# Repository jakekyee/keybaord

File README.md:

# Keyboard

## Quick Summary
A split inspired by the Quefrency.

# Build Guide
 - Placeholder
## BOM
 - Placeholder

# Firmware
https://github.com/jakekyee/zmk-config-stuff

# Techincal Notes  
The wiring on the right side is kinda crazy because I didn't really know what I was doing in KiCad. Here's the reference I used when writing the firmware.

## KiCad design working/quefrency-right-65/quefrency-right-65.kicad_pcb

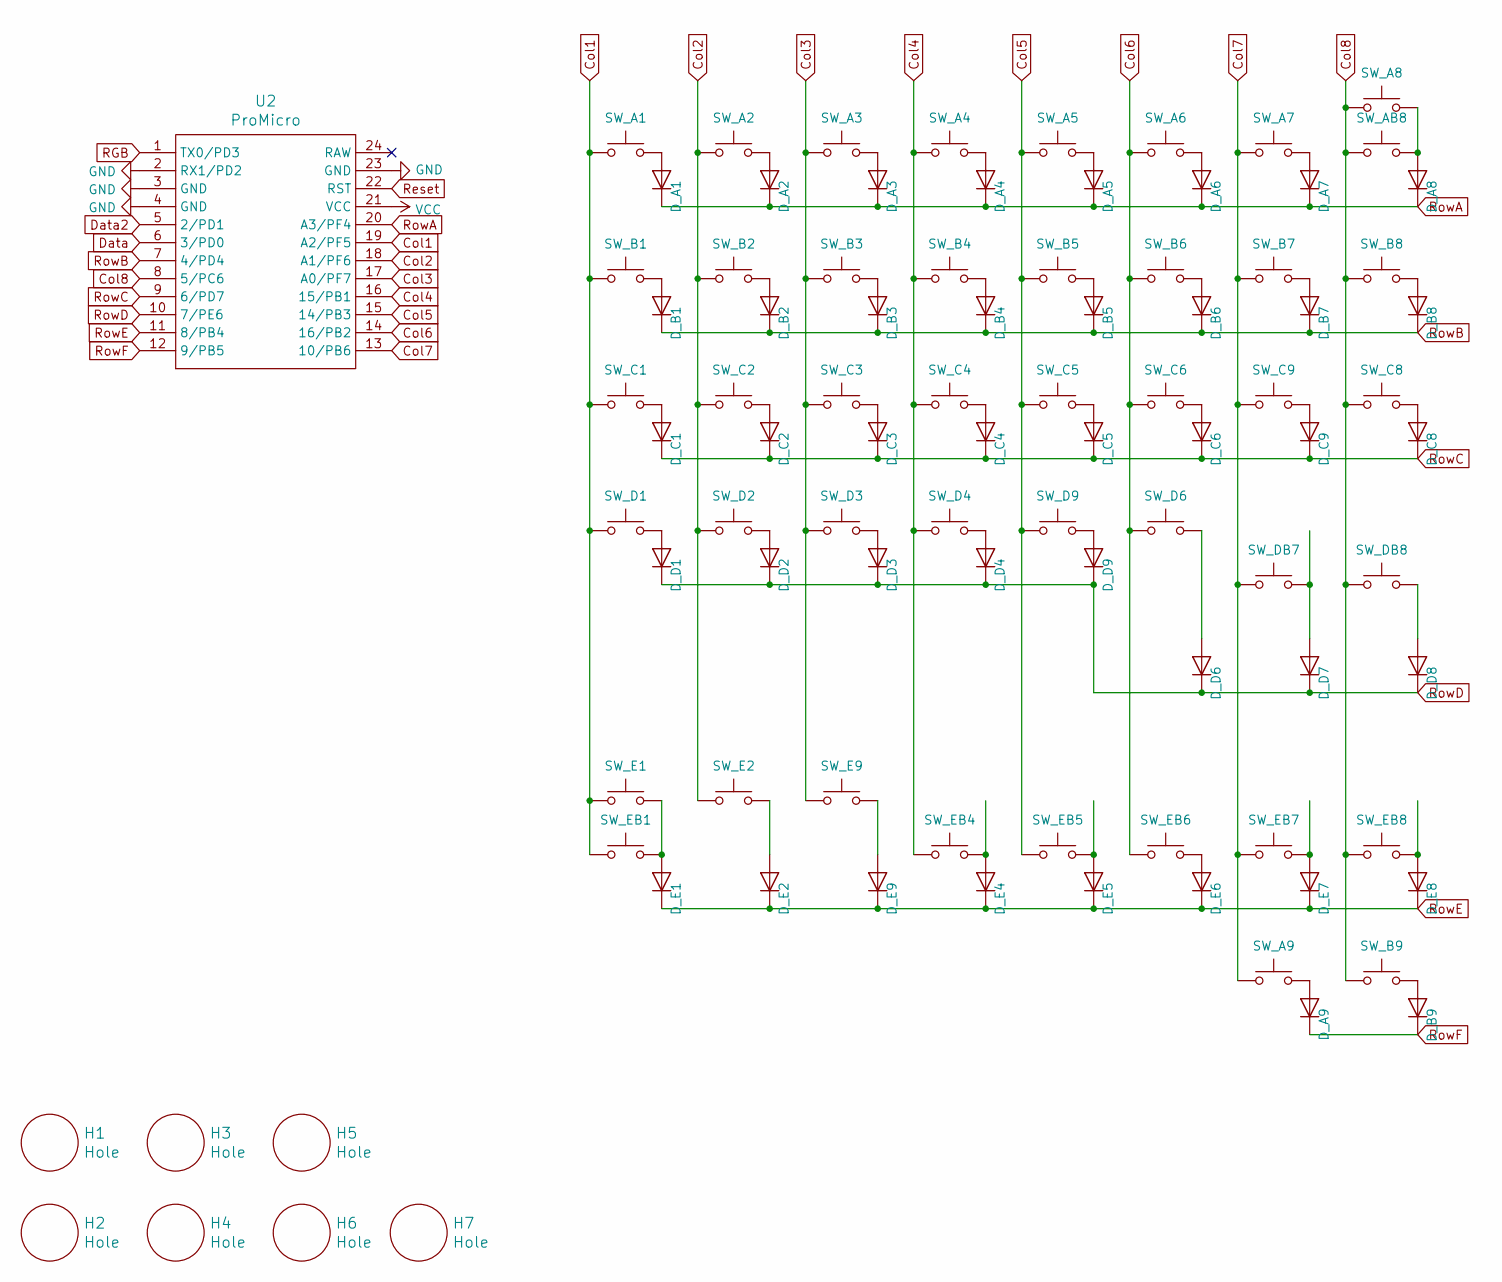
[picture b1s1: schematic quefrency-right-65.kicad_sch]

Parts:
D_A1, D_A2, D_A3, D_A4, D_A5, D_A6, D_A7, D_A8, D_A9: D; D_SOD-123
D_B1, D_B2, D_B3, D_B4, D_B5, D_B6, D_B7, D_B8, D_B9: D; D_SOD-123
D_C1, D_C2, D_C3, D_C4, D_C5, D_C6, D_C8, D_C9: D; D_SOD-123
D_D1, D_D2, D_D3, D_D4, D_D6, D_D7, D_D8, D_D9: D; D_SOD-123
D_E1, D_E2, D_E4, D_E5, D_E6, D_E7, D_E8, D_E9: D; D_SOD-123
H1, H2, H3, H4, H5, H6, H7: Hole; MountingHole_3.2mm_M3_ISO14580_Pad
SW_A1, SW_A2, SW_A3, SW_A4, SW_A5, SW_A6, SW_A9: SW_Push; ChocMX
SW_A7: SW_Push; ChocMX_sameside
SW_A8: SW_Push; ChocMX_sameside_flippedpads_2.25U
SW_AB8: SW_Push; ChocMX_sameside
SW_B1, SW_B2, SW_B3, SW_B4, SW_B5, SW_B6, SW_B7: SW_Push; ChocMX
SW_B8, SW_B9: SW_Push; ChocMX_sameside_flippedpads
SW_C1, SW_C2, SW_C3, SW_C4, SW_C5, SW_C6, SW_C9: SW_Push; ChocMX
SW_C8: SW_Push; ChocMX_flippedpads_2.25U
SW_D1, SW_D2, SW_D3, SW_D4, SW_D6, SW_D9: SW_Push; ChocMX
SW_DB7, SW_DB8: SW_Push; ChocMX
SW_E1: SW_Push; ChocMX_sameside_flippedpads_2.25U
SW_E2: SW_Push; ChocMX_sameside_flippedpads
SW_E9: SW_Push; ChocMX
SW_EB1: SW_Push; ChocMX_sameside
SW_EB4, SW_EB5, SW_EB6, SW_EB7, SW_EB8: SW_Push; ChocMX
U2: ProMicro; ArduinoProMicro-ZigZag

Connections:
Col1: SW_A1.1, SW_B1.1, SW_C1.1, SW_D1.1, SW_E1.1, SW_EB1.1, U2.19 (A2/PF5)
Col2: SW_A2.1, SW_B2.1, SW_C2.1, SW_D2.1, SW_E2.1, U2.18 (A1/PF6)
Col3: SW_A3.1, SW_B3.1, SW_C3.1, SW_D3.1, SW_E9.1, U2.17 (A0/PF7)
Col4: SW_A4.1, SW_B4.1, SW_C4.1, SW_D4.1, SW_EB4.1, U2.16 (15/PB1)
Col5: SW_A5.1, SW_B5.1, SW_C5.1, SW_D9.1, SW_EB5.2, U2.15 (14/PB3)
Col6: SW_A6.1, SW_B6.1, SW_C6.1, SW_D6.1, SW_EB6.1, U2.14 (16/PB2)
Col7: SW_A7.1, SW_A9.1, SW_B7.1, SW_C9.1, SW_DB7.1, SW_EB7.2, U2.13 (10/PB6)
Col8: SW_A8.1, SW_AB8.1, SW_B8.1, SW_B9.1, SW_C8.1, SW_DB8.1, SW_EB8.1, U2.8 (5/PC6)
Data: U2.6 (3/PD0)
Data2: U2.5 (2/PD1)
GND: U2.2 (RX1/PD2), U2.3 (GND), U2.4 (GND), U2.23 (GND)
unnamed: D_A1.2 (A), SW_A1.2
unnamed: D_A2.2 (A), SW_A2.2
unnamed: D_A3.2 (A), SW_A3.2
unnamed: D_A4.2 (A), SW_A4.2
unnamed: D_A5.2 (A), SW_A5.2
unnamed: D_A6.2 (A), SW_A6.2
unnamed: D_A7.2 (A), SW_A7.2
unnamed: D_A8.2 (A), SW_A8.2, SW_AB8.2
unnamed: D_A9.2 (A), SW_A9.2
unnamed: D_B1.2 (A), SW_B1.2
unnamed: D_B2.2 (A), SW_B2.2
unnamed: D_B3.2 (A), SW_B3.2
unnamed: D_B4.2 (A), SW_B4.2
unnamed: D_B5.2 (A), SW_B5.2
unnamed: D_B6.2 (A), SW_B6.2
unnamed: D_B7.2 (A), SW_B7.2
unnamed: D_B8.2 (A), SW_B8.2
unnamed: D_B9.2 (A), SW_B9.2
unnamed: D_C1.2 (A), SW_C1.2
unnamed: D_C2.2 (A), SW_C2.2
unnamed: D_C3.2 (A), SW_C3.2
unnamed: D_C4.2 (A), SW_C4.2
unnamed: D_C5.2 (A), SW_C5.2
unnamed: D_C6.2 (A), SW_C6.2
unnamed: D_C8.2 (A), SW_C8.2
unnamed: D_C9.2 (A), SW_C9.2
unnamed: D_D1.2 (A), SW_D1.2
unnamed: D_D2.2 (A), SW_D2.2
unnamed: D_D3.2 (A), SW_D3.2
unnamed: D_D4.2 (A), SW_D4.2
unnamed: D_D6.2 (A), SW_D6.2
unnamed: D_D7.2 (A), SW_DB7.2
unnamed: D_D8.2 (A), SW_DB8.2
unnamed: D_D9.2 (A), SW_D9.2
unnamed: D_E1.2 (A), SW_E1.2, SW_EB1.2
unnamed: D_E2.2 (A), SW_E2.2
unnamed: D_E4.2 (A), SW_EB4.2
unnamed: D_E5.2 (A), SW_EB5.1
unnamed: D_E6.2 (A), SW_EB6.2
unnamed: D_E7.2 (A), SW_EB7.1
unnamed: D_E8.2 (A), SW_EB8.2
unnamed: D_E9.2 (A), SW_E9.2
RGB: U2.1 (TX0/PD3)
Reset: U2.22 (RST)
RowA: D_A1.1 (K), D_A2.1 (K), D_A3.1 (K), D_A4.1 (K), D_A5.1 (K), D_A6.1 (K), D_A7.1 (K), D_A8.1 (K), U2.20 (A3/PF4)
RowB: D_B1.1 (K), D_B2.1 (K), D_B3.1 (K), D_B4.1 (K), D_B5.1 (K), D_B6.1 (K), D_B7.1 (K), D_B8.1 (K), U2.7 (4/PD4)
RowC: D_C1.1 (K), D_C2.1 (K), D_C3.1 (K), D_C4.1 (K), D_C5.1 (K), D_C6.1 (K), D_C8.1 (K), D_C9.1 (K), U2.9 (6/PD7)
RowD: D_D1.1 (K), D_D2.1 (K), D_D3.1 (K), D_D4.1 (K), D_D6.1 (K), D_D7.1 (K), D_D8.1 (K), D_D9.1 (K), U2.10 (7/PE6)
RowE: D_E1.1 (K), D_E2.1 (K), D_E4.1 (K), D_E5.1 (K), D_E6.1 (K), D_E7.1 (K), D_E8.1 (K), D_E9.1 (K), U2.11 (8/PB4)
RowF: D_A9.1 (K), D_B9.1 (K), U2.12 (9/PB5)
VCC: U2.21 (VCC)

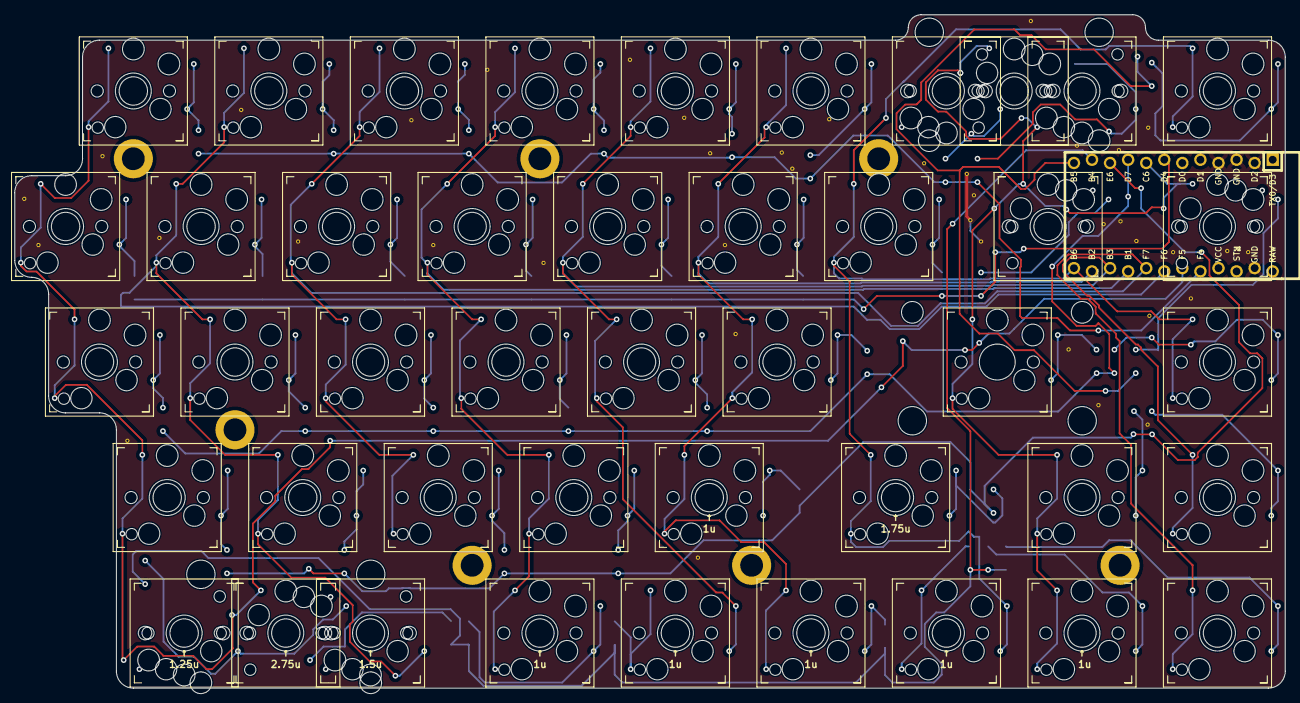
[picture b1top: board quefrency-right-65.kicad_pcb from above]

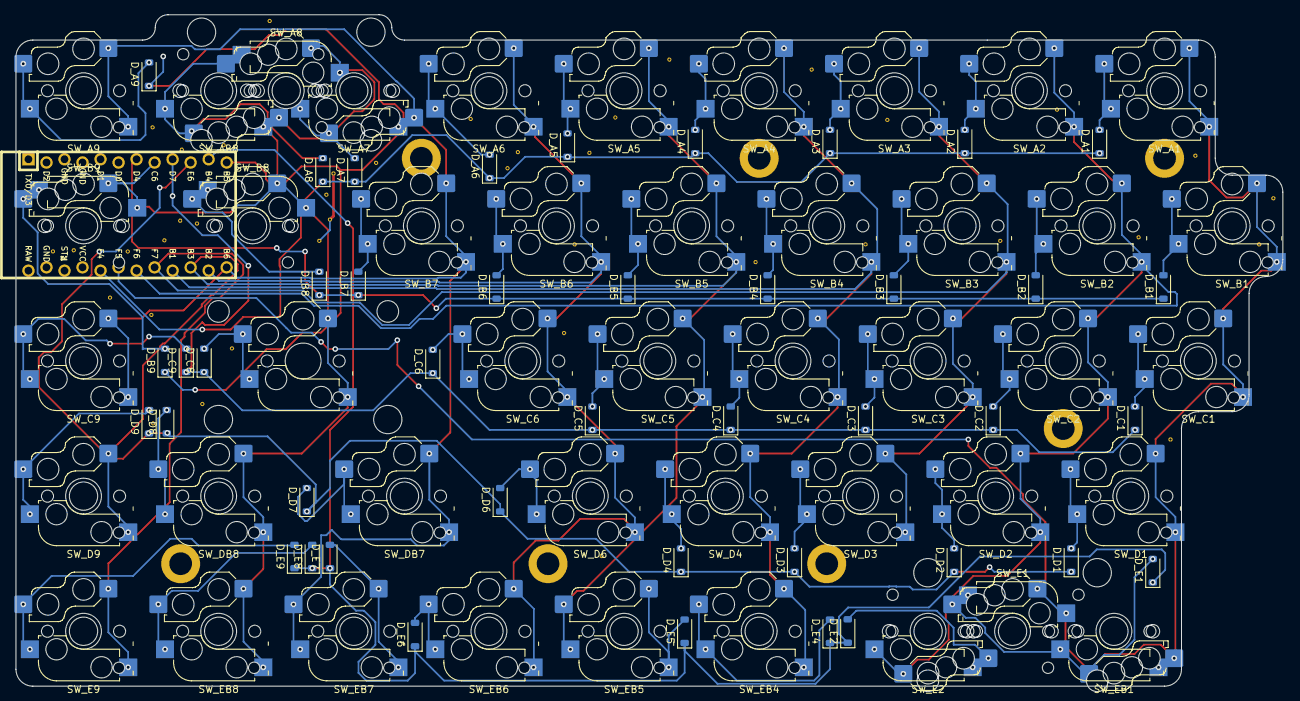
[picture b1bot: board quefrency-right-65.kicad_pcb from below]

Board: 2 copper layers, 178.6 x 94.7 mm, 94 parts (42 on the bottom side), 57 nets.

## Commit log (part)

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2026-03-12 Revert "Initial commit"
    This reverts commit 2875743805b97efa5c6224fbcc698e079b912aaf.
2026-03-13 updated footprints?
2026-03-26 test
2026-03-26 added working dir
2026-03-26 fixed stuff
2026-03-28 changed footprints, still have to route
2026-03-28 swapped left side footprints, still have to route
2026-05-07 Upodated stuff, finalish version for left
